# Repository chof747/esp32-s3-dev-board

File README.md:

# ESP32-S3 Development Board
Minimal development board for an ESP32-S3 MCU.

It contains the following elements:

- ESP32 MCU with all available pins broken out
- Programming header with DTR/RTS mechanism
- Power LED
- Fuse to prevent the worse
- Jumper to disconnect 3v3 from the programmer to be able to test e.g. battery mode while still debugging
- A 3V3 regulator to allow connection via an USB Breakout

## Used Parts:

## Revision History:

- **v1.0**: Initial version (filed for fabrication: 19.11.2022, first successfull assembly: 29.11.2022)
- **v1.1**: Changed serial programmer to UMH3 chip and added boot button
- **v1.2**: Changed to slim version that fits on a breadboard leaving one row of connections on the left and right.

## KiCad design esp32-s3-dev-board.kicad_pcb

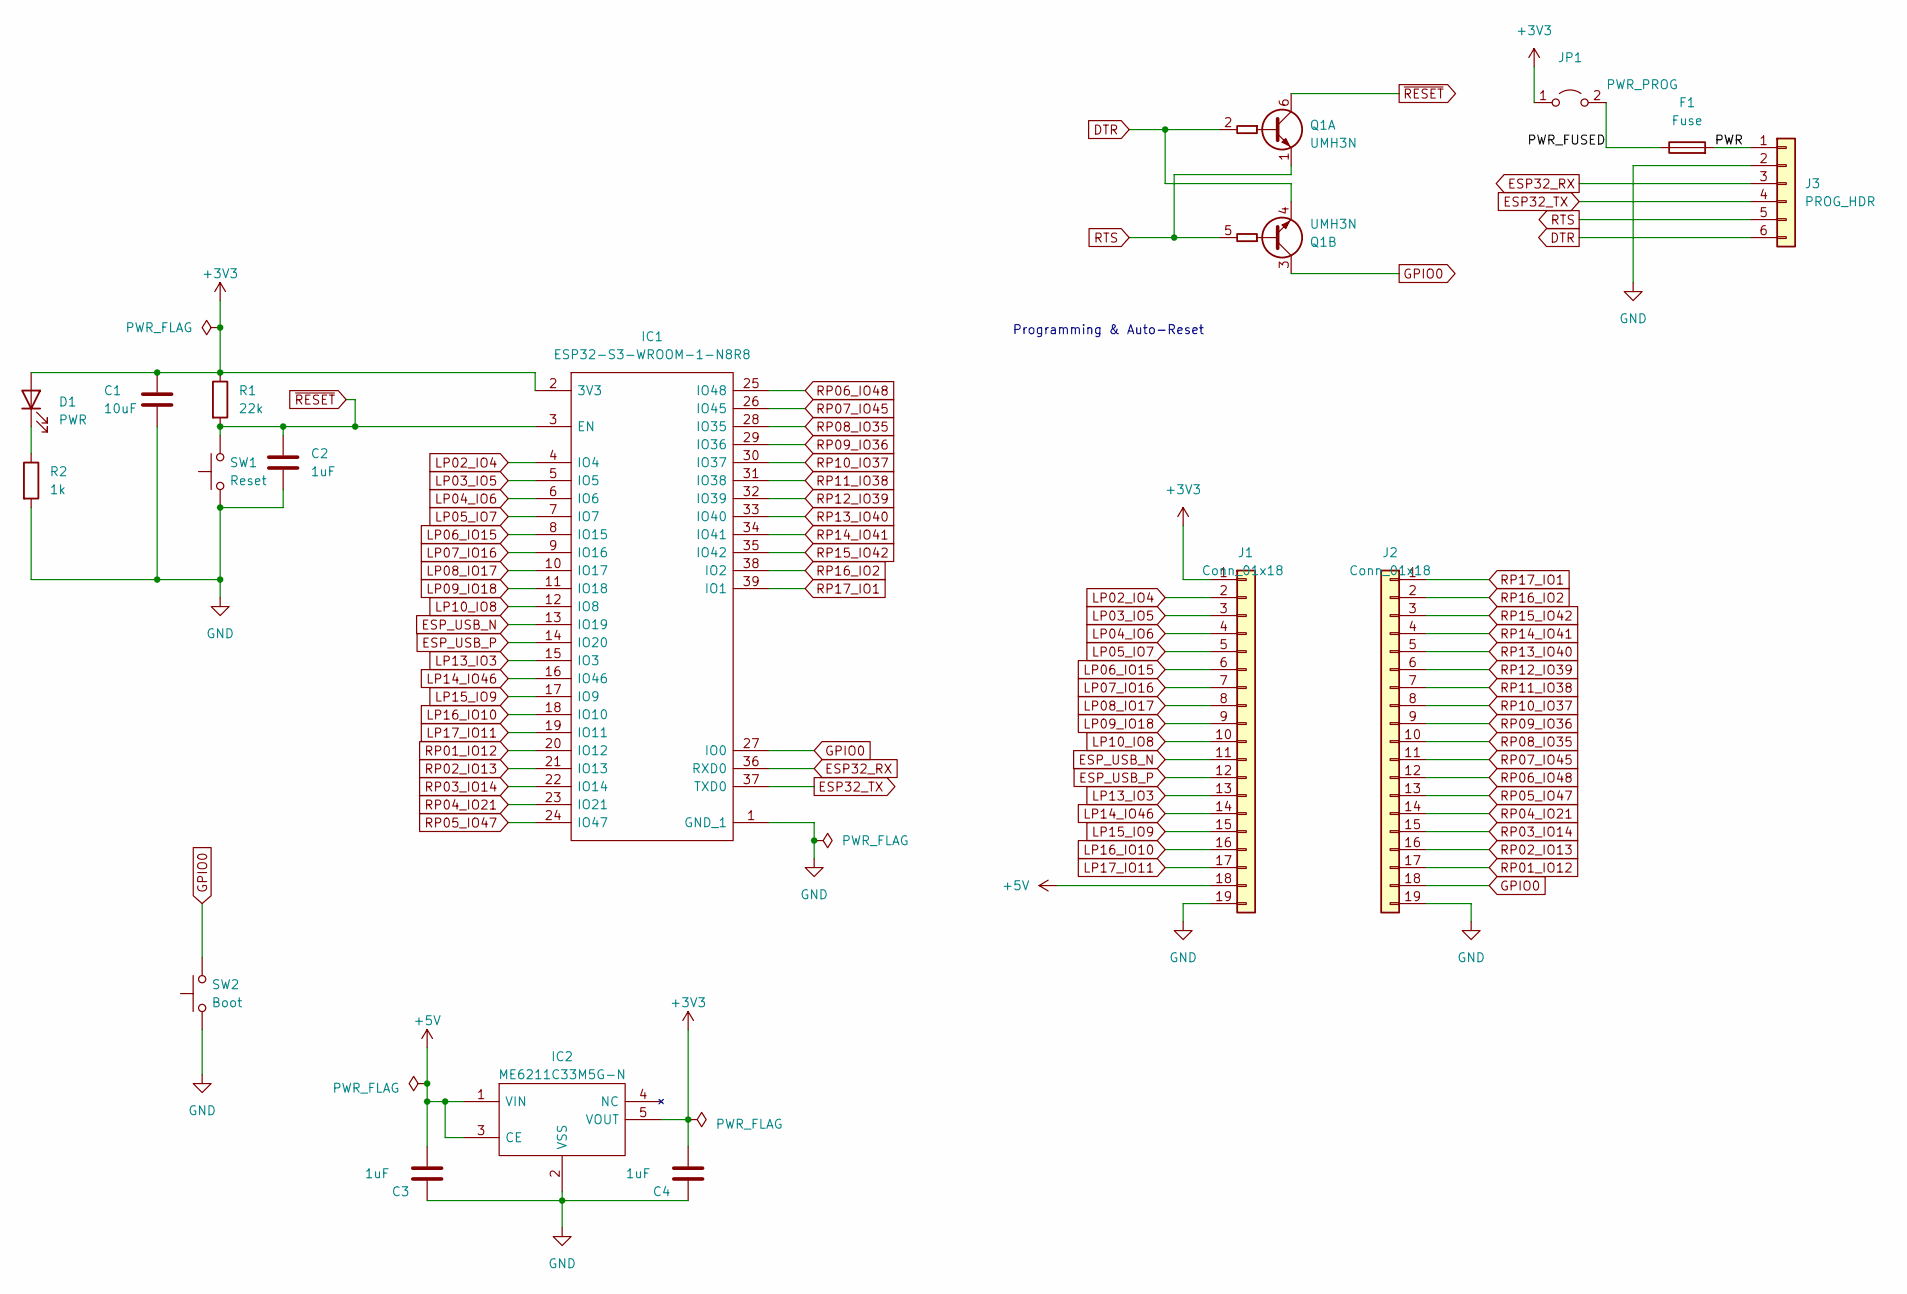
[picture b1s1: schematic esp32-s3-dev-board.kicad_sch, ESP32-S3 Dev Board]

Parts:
C1: 10uF; C_0603_1608Metric_Pad1.08x0.95mm_HandSolder
C2, C3, C4: 1uF; C_0603_1608Metric_Pad1.08x0.95mm_HandSolder
D1: PWR; LED_0603_1608Metric_Pad1.05x0.95mm_HandSolder
F1: Fuse; Fuse_1206_3216Metric_Pad1.42x1.75mm_HandSolder
IC1: ESP32-S3-WROOM-1-N8R8; ESP32S3WROOM1N8R8; Manufacturer_Part_Number ESP32-S3-WROOM-1-N8R8; Mouser Part Number 356-EP32S3WROOM1N8R8
IC2: ME6211C33M5G-N; SOT95P270X145-5N; Manufacturer_Part_Number ME6211C33M5G-N
J1, J2: Conn_01x18; PinHeader_1x19_P2.54mm_Vertical
J3: PROG_HDR; PinHeader_1x06_P2.54mm_Vertical
JP1: PWR_PROG; PinHeader_1x02_P2.54mm_Vertical
Q1: UMH3N; SOT-363_SC-70-6
R1: 22k; R_0603_1608Metric_Pad0.98x0.95mm_HandSolder
R2: 1k; R_0603_1608Metric_Pad0.98x0.95mm_HandSolder
SW1: Reset; SW_PUSH_6mm
SW2: Boot; SW_PUSH_6mm

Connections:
GPIO0: IC1.27 (IO0), J2.18, Q1.3 (C2), SW2.2
+3V3: C1.1, C4.1, D1.2 (A), IC1.2 (3V3), IC2.5 (VOUT), J1.1, JP1.1 (A), R1.1
+5V: C3.1, IC2.1 (VIN), IC2.3 (CE), J1.18
/PWR: F1.2, J3.1
/PWR_FUSED: F1.1, JP1.2 (B)
DTR: J3.6, Q1.2 (B1), Q1.4 (E2)
ESP32_RX: IC1.36 (RXD0), J3.3
ESP32_TX: IC1.37 (TXD0), J3.4
ESP_USB_N: IC1.13 (IO19), J1.11
ESP_USB_P: IC1.14 (IO20), J1.12
GND: C1.2, C2.2, C3.2, C4.2, IC1.1 (GND_1), IC2.2 (VSS), J1.19, J2.19, J3.2, R2.2, SW1.1, SW2.1
LP02_IO4: IC1.4 (IO4), J1.2
LP03_IO5: IC1.5 (IO5), J1.3
LP04_IO6: IC1.6 (IO6), J1.4
LP05_IO7: IC1.7 (IO7), J1.5
LP06_IO15: IC1.8 (IO15), J1.6
LP07_IO16: IC1.9 (IO16), J1.7
LP08_IO17: IC1.10 (IO17), J1.8
LP09_IO18: IC1.11 (IO18), J1.9
LP10_IO8: IC1.12 (IO8), J1.10
LP13_IO3: IC1.15 (IO3), J1.13
LP14_IO46: IC1.16 (IO46), J1.14
LP15_IO9: IC1.17 (IO9), J1.15
LP16_IO10: IC1.18 (IO10), J1.16
LP17_IO11: IC1.19 (IO11), J1.17
unnamed: D1.1 (K), R2.1
RP01_IO12: IC1.20 (IO12), J2.17
RP02_IO13: IC1.21 (IO13), J2.16
RP03_IO14: IC1.22 (IO14), J2.15
RP04_IO21: IC1.23 (IO21), J2.14
RP05_IO47: IC1.24 (IO47), J2.13
RP06_IO48: IC1.25 (IO48), J2.12
RP07_IO45: IC1.26 (IO45), J2.11
RP08_IO35: IC1.28 (IO35), J2.10
RP09_IO36: IC1.29 (IO36), J2.9
RP10_IO37: IC1.30 (IO37), J2.8
RP11_IO38: IC1.31 (IO38), J2.7
RP12_IO39: IC1.32 (IO39), J2.6
RP13_IO40: IC1.33 (IO40), J2.5
RP14_IO41: IC1.34 (IO41), J2.4
RP15_IO42: IC1.35 (IO42), J2.3
RP16_IO2: IC1.38 (IO2), J2.2
RP17_IO1: IC1.39 (IO1), J2.1
RTS: J3.5, Q1.1 (E1), Q1.5 (B2)
~RESET: C2.1, IC1.3 (EN), Q1.6 (C1), R1.2, SW1.2

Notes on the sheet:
Programming & Auto-Reset

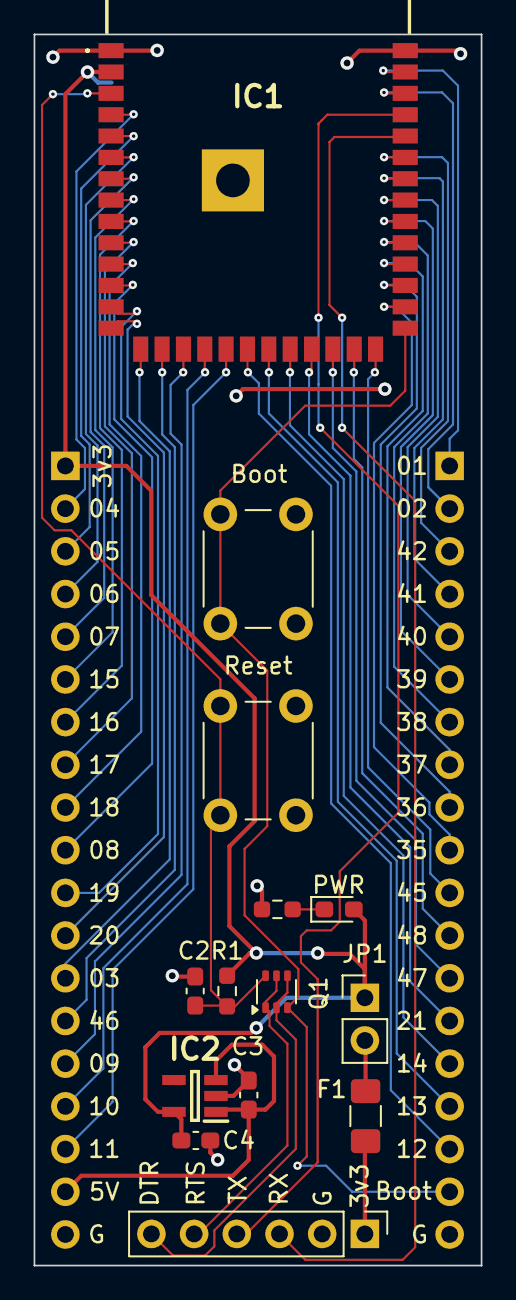
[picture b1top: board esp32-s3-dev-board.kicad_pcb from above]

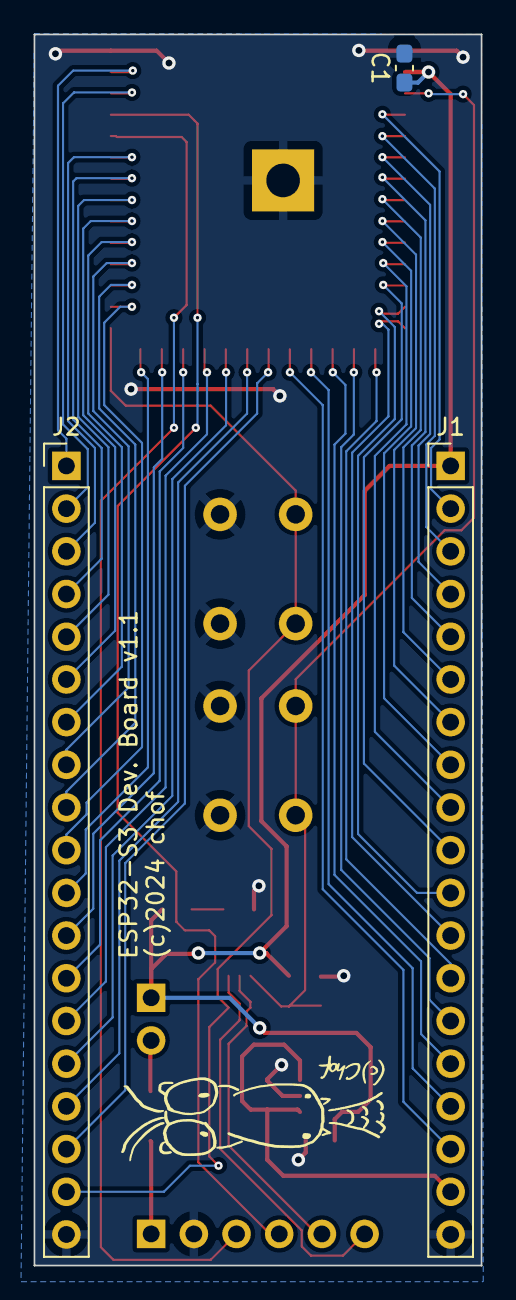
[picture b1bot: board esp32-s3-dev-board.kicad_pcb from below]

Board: 2 copper layers, 26.6 x 73.2 mm, 17 parts (3 on the bottom side), 45 nets.

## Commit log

2022-11-20 Initial revision of esp32-dev-board
2022-12-01 Added Example firmwares after first board assembly
    - Added a rudimentary custom build firmware
    - Added a basic esphome configuration
    - Documented first assembly
2023-04-19 Added test code
2023-04-27 Updated template for KiCAD 7
2024-03-15 Changed reset circuit to UMH3N and Upgrade to KiCad 8
2024-07-18 added *.lck to gitignore
2024-07-18 Added version 1.1 with following changes:
    - Changed reset and boot logic to UMH3 chip
    - Added a boot button to allow manual setting into boot mode
2024-07-25 removed old production mechanism
2024-07-25 added new production mechanism
2024-07-25 changed to slim board design - Made the board smaller so that it fits on a breadboard and leaves room for a slot on the left and right - Added a 3v3 Regulator to allow connection via an USB Breakout

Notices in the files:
esp32-s3-dev-board.kicad_pcb:
(c)2024 chof
